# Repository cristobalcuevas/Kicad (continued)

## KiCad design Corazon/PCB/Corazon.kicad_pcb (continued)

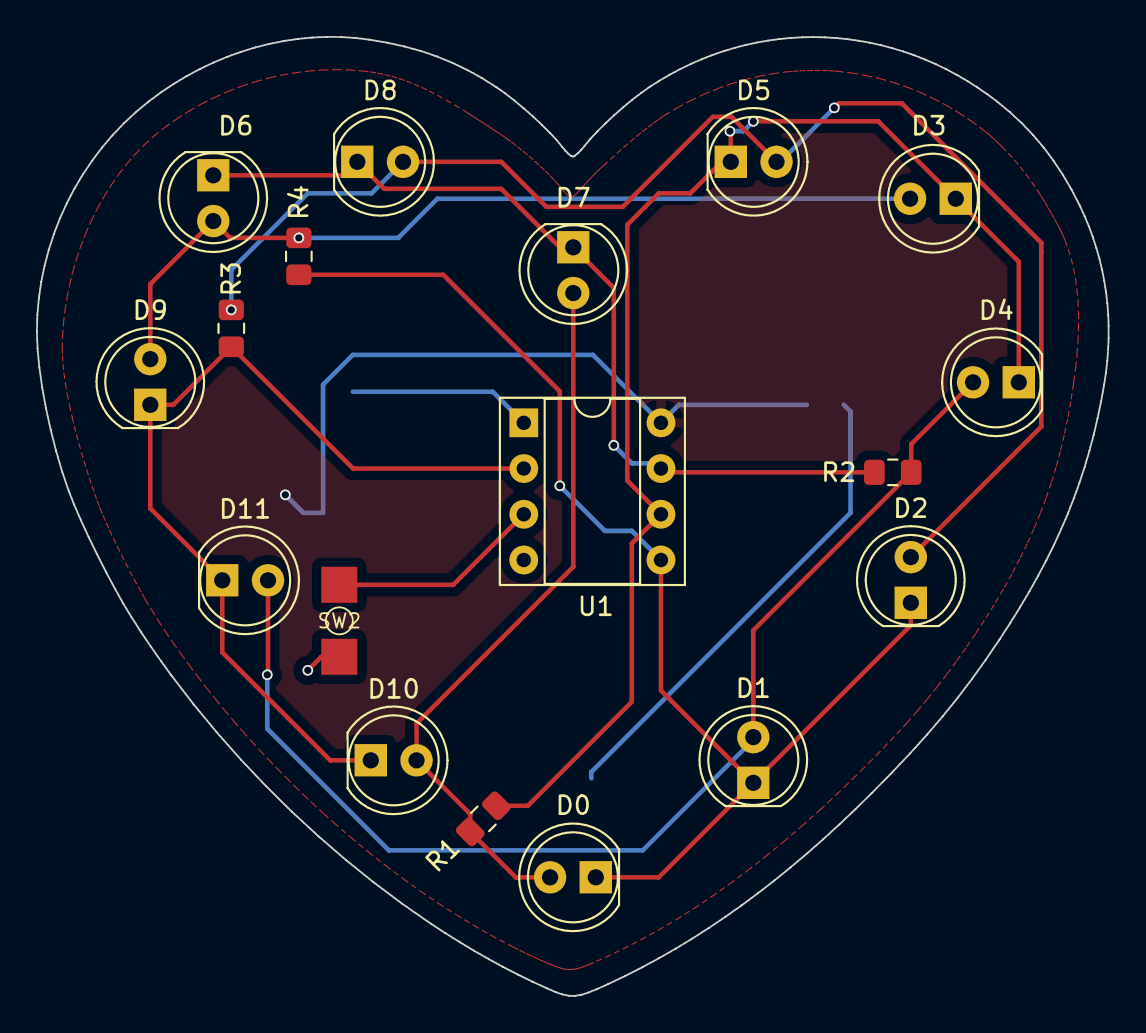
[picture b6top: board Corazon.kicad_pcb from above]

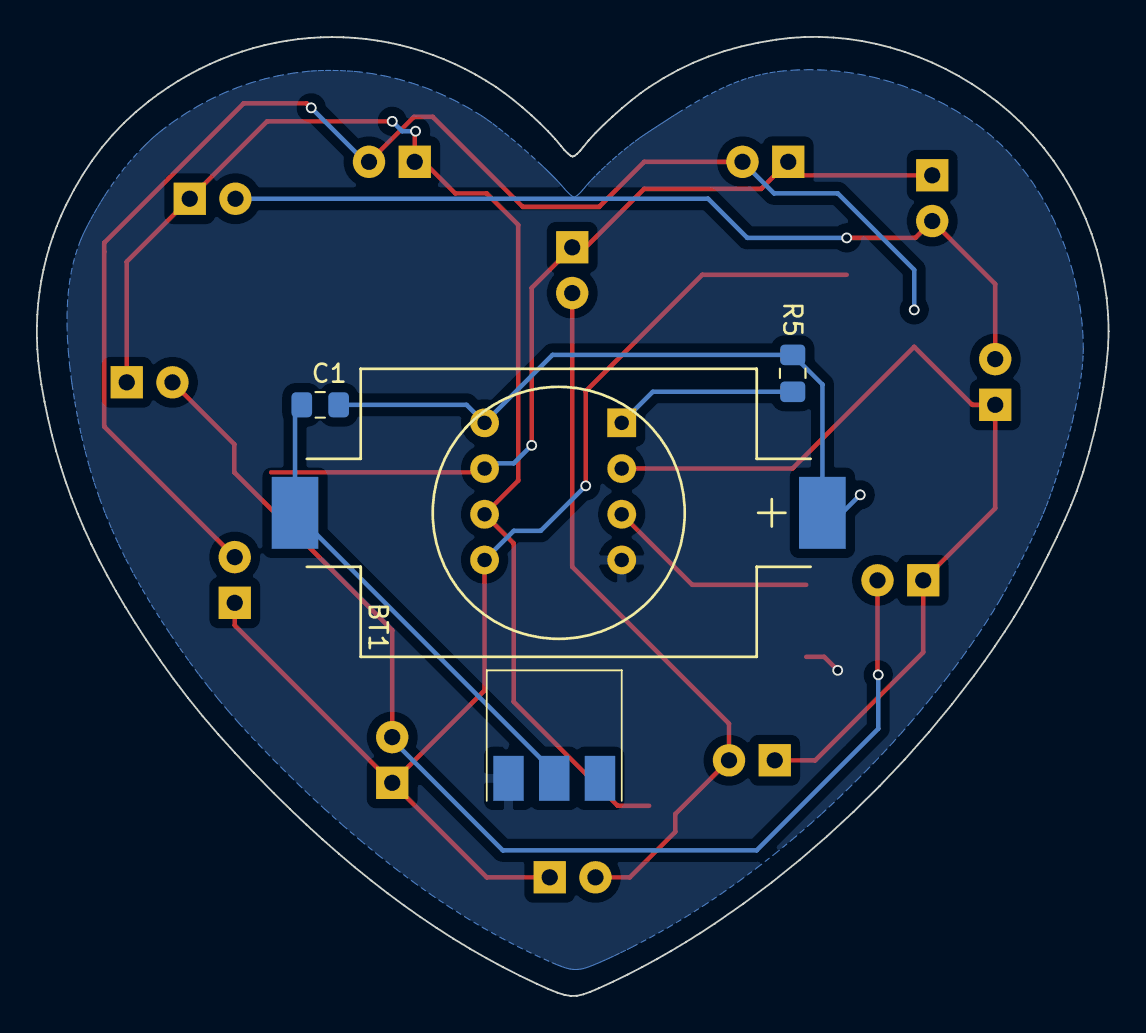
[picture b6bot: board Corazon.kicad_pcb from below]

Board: 2 copper layers, 59.5 x 53.3 mm, 22 parts (4 on the bottom side), 13 nets.

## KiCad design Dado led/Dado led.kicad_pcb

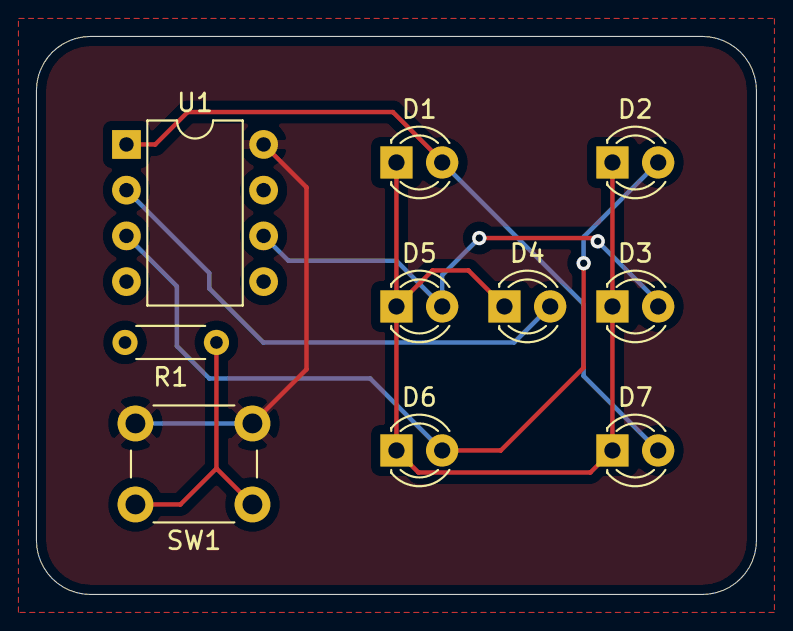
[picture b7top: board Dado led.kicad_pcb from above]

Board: 2 copper layers, 40.0 x 31.0 mm, 10 parts (0 on the bottom side), 8 nets.

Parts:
D1, D2, D3, D4, D5, D6, D7: LED; LED_D3.0mm
R1: 10k; R_Axial_DIN0204_L3.6mm_D1.6mm_P5.08mm_Horizontal
SW1: SWITCH; SW_PUSH_6mm_H5mm
U1: ATtiny85-20PU; DIP-8_W7.62mm

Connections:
+3V3: SW1.2, U1.8
GND: R1.2, U1.4
unnamed: D1.1, D2.1, D3.1, D4.1, D5.1, D6.1, D7.1
unnamed: D1.2, D7.2, U1.1
unnamed: D2.2, D6.2, U1.3
unnamed: D3.2, D5.2, U1.6
unnamed: D4.2, U1.2
unnamed: R1.1, SW1.1
